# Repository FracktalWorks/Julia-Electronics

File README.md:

# Julia-Electronics
Boards and other electronics for Julia 2018 Series of 3D Printers( Extended, Advanced, Intermediate, Classic)

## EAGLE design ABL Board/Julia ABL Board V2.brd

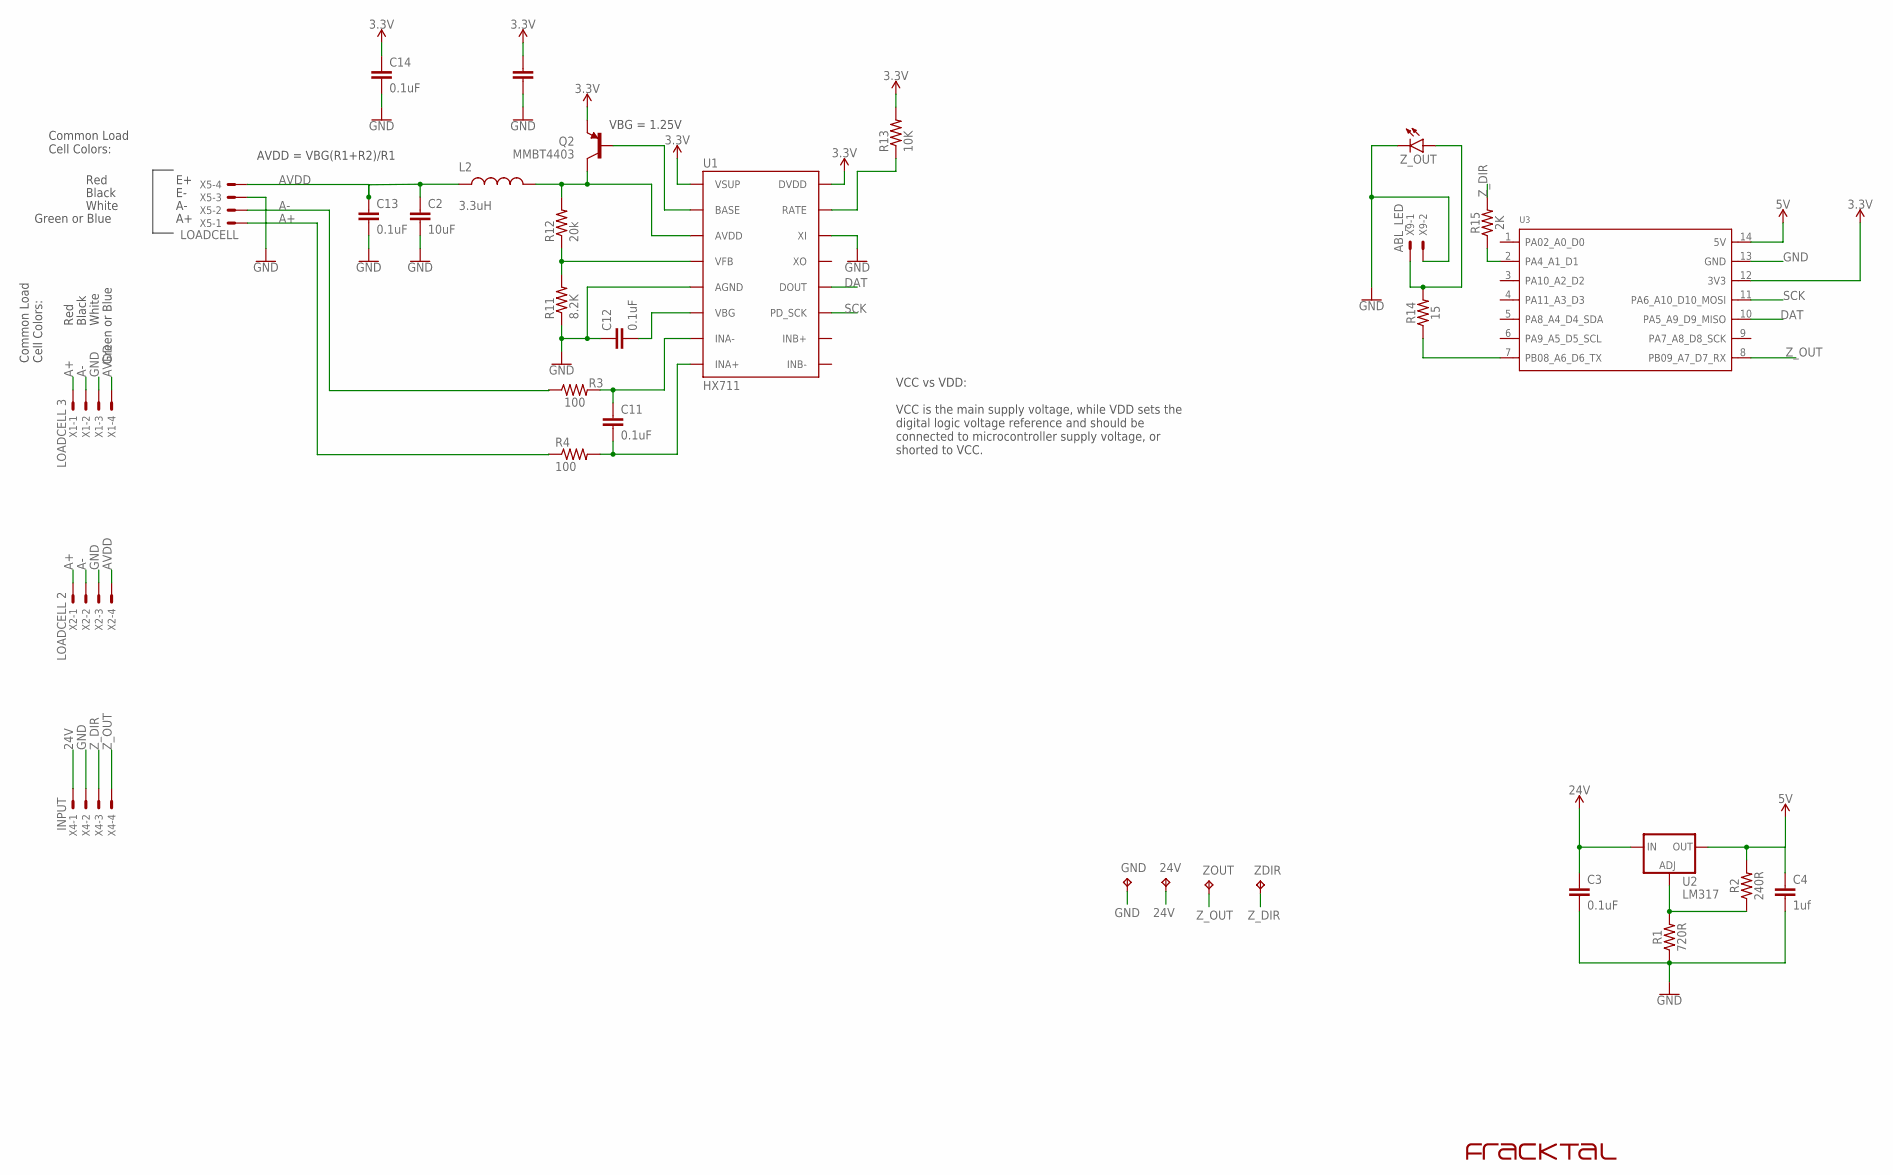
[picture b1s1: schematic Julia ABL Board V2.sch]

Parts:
24V: TPB2,54; B2,54
C1, C2: 10uF; 1210
C3: 0.1uF; 0603
C4: 1uf; 0603
C11, C12, C13, C14: 0.1uF; 0603-CAP
GND: TPB2,54; B2,54
L2: 3.3uH; 0805
Q2: MMBT4403; SOT23-3
R1: 720R; 0603
R2: 240R; 0603
R3, R4: 100; 0603-RES
R11: 8.2K; 0603-RES
R12: 20k; 0603-RES
R13: 10K; 0603-RES
R14: 15; 0603
R15: 2K; 0603
U1: HX711; SO16
U2: LM317; SOT223
U3: MOUDLE-SEEEDUINO-XIAO; MOUDLE14P-2.54-21X17.8MM
U$2: FRACKTALLOGO
X1: LOADCELL 3; JST-XH-04-PACKAGE-LONG-PAD
X2: LOADCELL 2; JST-XH-04-PACKAGE-LONG-PAD
X4: INPUT; JST-XH-04-PACKAGE-LONG-PAD
X5: LOADCELL; JST-XH-04-PACKAGE-LONG-PAD
X9: ABL_LED; JST-XH-02-PACKAGE-LONG-PAD
ZDIR: TPB2,54; B2,54
ZOUT: TPB2,54; B2,54
Z_OUT: LEDSML0603; SML0603

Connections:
3.3V: C1.1, C14.1, Q2.2 (E), R13.2, U1.1 (VSUP), U1.16 (DVDD), U3.12 (3V3)
5V: C4.1, R2.2, U2.2 (OUT), U3.14 (5V)
24V: 24V.TP, C3.1, U2.3 (IN), X4.1
A+: R4.1, X1.1, X2.1, X5.1
A-: R3.1, X1.2, X2.2, X5.2
ADJ: R1.2, R2.1, U2.1 (ADJ)
AVDD: C2.1, C13.1, L2.1, X1.4, X2.4, X5.4
DAT: U1.12 (DOUT), U3.10 (PA5_A9_D9_MISO)
GND: C1.2, C2.2, C3.2, C4.2, C12.1, C13.2, C14.2, GND.TP, R1.1, R11.1, U1.5 (AGND), U1.14 (XI), U3.13 (GND), X1.3, X2.3, X4.2, X5.3, X9.2, Z_OUT.C
unnamed: Q2.1 (B), U1.2 (BASE)
unnamed: R11.2, R12.1, U1.4 (VFB)
unnamed: C12.2, U1.6 (VBG)
unnamed: L2.2, Q2.3 (C), R12.2, U1.3 (AVDD)
unnamed: R13.1, U1.15 (RATE)
unnamed: C11.1, R3.2, U1.7 (INA-)
unnamed: C11.2, R4.2, U1.8 (INA+)
unnamed: R14.2, X9.1, Z_OUT.A
unnamed: R14.1, U3.7 (PB08_A6_D6_TX)
unnamed: R15.1, U3.2 (PA4_A1_D1)
SCK: U1.11 (PD_SCK), U3.11 (PA6_A10_D10_MOSI)
Z_DIR: R15.2, X4.3, ZDIR.TP
Z_OUT: U3.8 (PB09_A7_D7_RX), X4.4, ZOUT.TP

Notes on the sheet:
Red
Black
White
Green or Blue
Common Load Cell Colors:
VBG = 1.25V
AVDD = VBG(R1+R2)/R1
VCC vs VDD: VCC is the main supply voltage, while VDD sets the digital logic voltage reference and should be connected to microcontroller supply voltage, or shorted to VCC.

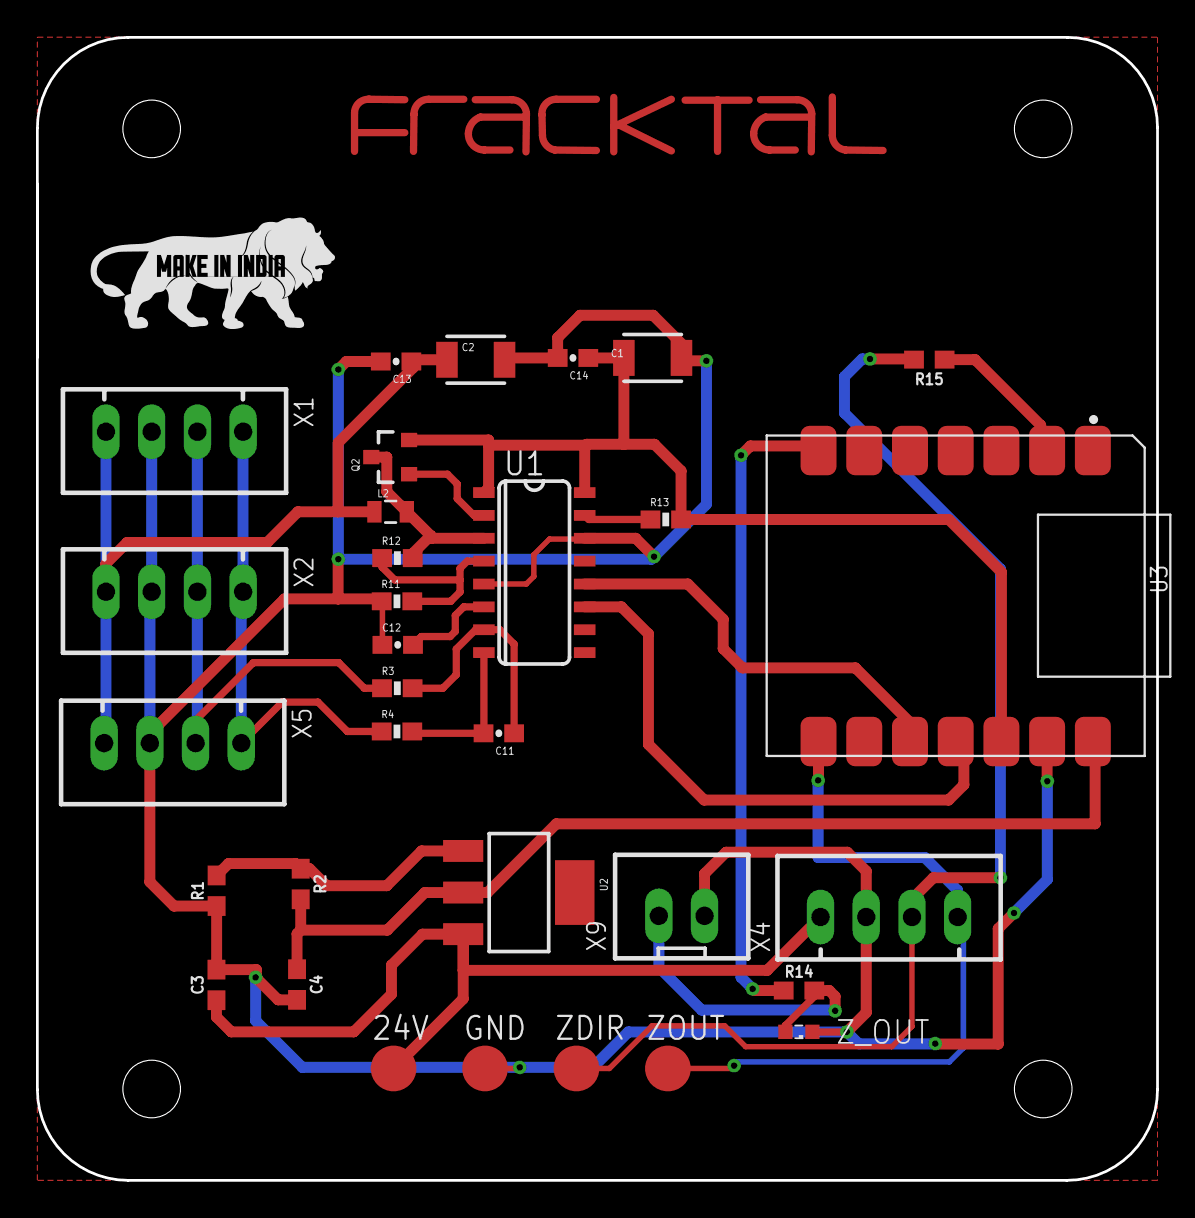
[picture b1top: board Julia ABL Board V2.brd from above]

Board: 2 copper layers, 62.2 x 63.5 mm, 34 parts (0 on the bottom side), 22 nets.

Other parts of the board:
U$1: MAKEININDIA

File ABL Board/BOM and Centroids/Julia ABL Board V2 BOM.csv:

Qty,Designator,Footprint,Comment,LCSC Part #,Description,Value
1,Z_OUT,SML0603,LEDSML0603,,LED,
1,U3,MOUDLE14P-2.54-21X17.8MM,MOUDLE-SEEEDUINO-XIAO,,,
1,R1,603,RESISTOR0603,,Generic Resistor Package, 720R
4,"C11, C12, C13, C14",0603-CAP,0.1UF-25V-5%(0603),,CAP-08604,0.1uF
1,C3,603,9.0PF-0603-50V-10%,,9.0pF ceramic capacitors,0.1uF
2,"R3, R4",0603-RES,100OHM-1/10W-1%(0603),,RES-07863,100
1,R13,0603-RES,10KOHM-1/10W-1%(0603)0603,,RES-00824,10K
2,"C1, C2",1210,10UF50V20%(1210),,CAP-09824,10uF
1,R14,603,RESISTOR0603,,Generic Resistor Package,15
1,C4,603,9.0PF-0603-50V-10%,,9.0pF ceramic capacitors,1uf
1,R12,0603-RES,20KOHM1/10W1%(0603),,RES-09383,20k
1,R2,603,RESISTOR0603,,Generic Resistor Package,240R
1,R15,603,RESISTOR0603,,Generic Resistor Package,2K
1,L2,805,INDUCTOR0805-IND,,Inductors,3.3uH
1,R11,0603-RES,8.2KOHM-1/10W-5%(0603),,RES-10646,8.2K
1,X9,JST-XH-02-PACKAGE-LONG-PAD,JST-XH-02-PIN-LONG-PAD,,JST XH Connector 2 Pin,ABL_LED
1,U$2,FRACKTALLOGO,FRACKTALLOGO,,,FRACKTALLOGO
1,U1,SO16,HX711HX711,,,HX711
1,X4,JST-XH-04-PACKAGE-LONG-PAD,JST-XH-04-PIN-LONG-PAD,,JST XH Connector 2 Pin,INPUT
1,U2,SOT223,V_REG_317SMD,,Voltage Regulator,LM317
1,X5,JST-XH-04-PACKAGE-LONG-PAD,JST-XH-04-PIN-LONG-PAD,,JST XH Connector 2 Pin,LOADCELL
1,X2,JST-XH-04-PACKAGE-LONG-PAD,JST-XH-04-PIN-LONG-PAD,,JST XH Connector 2 Pin,LOADCELL 2
1,X1,JST-XH-04-PACKAGE-LONG-PAD,JST-XH-04-PIN-LONG-PAD,,JST XH Connector 2 Pin,LOADCELL 3
1,Q2,SOT23-3,TRANSISTOR_PNPMMBT4403,,Generic PNP BJT,MMBT4403
4,"24V, GND, ZDIR, ZOUT","B2,54","TPB2,54",,Test pad,"TPB2,54"

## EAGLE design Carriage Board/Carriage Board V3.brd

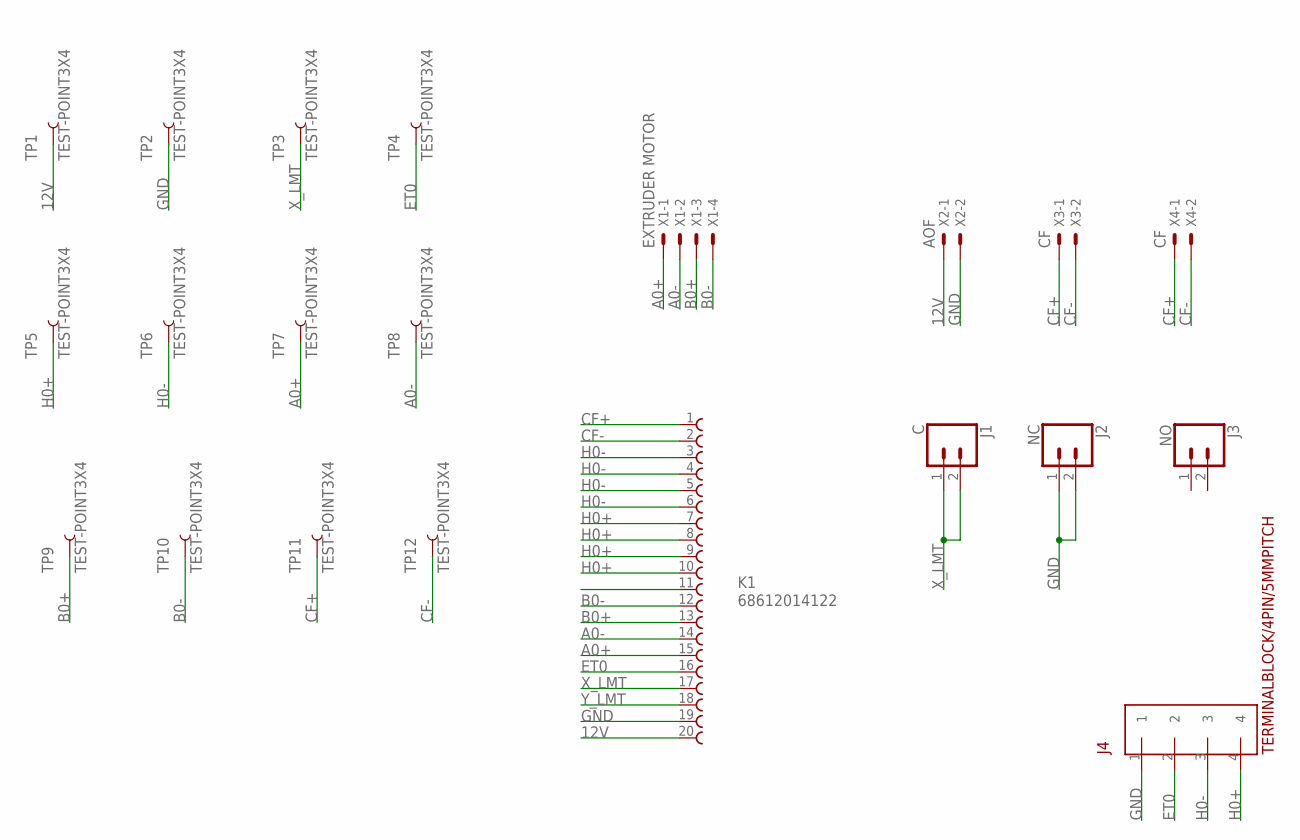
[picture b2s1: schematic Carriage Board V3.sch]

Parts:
J1: C; 1X02
J2: NC; 1X02
J3: NO; 1X02
J4: TERMINALBLOCK/4PIN/5MMPITCH; TERMINALBLOCK/TOYO/4PIN/5MMPITCH
K1: 68612014122
TP1, TP2, TP3, TP4, TP5, TP6, TP7, TP8, TP9, TP10, TP11, TP12: TEST-POINT3X4; PAD.03X.04
X1: EXTRUDER MOTOR; JST-XH-04-PACKAGE-LONG-PAD
X2: AOF; JST-XH-02-PACKAGE-LONG-PAD
X3, X4: CF; JST-XH-02-PACKAGE-LONG-PAD

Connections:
12V: K1.20, TP1.P$1, X2.1
A0+: K1.15, TP7.P$1, X1.1
A0-: K1.14, TP8.P$1, X1.2
B0+: K1.13, TP9.P$1, X1.3
B0-: K1.12, TP10.P$1, X1.4
CF+: K1.1, TP11.P$1, X3.1, X4.1
CF-: K1.2, TP12.P$1, X3.2, X4.2
ET0: J4.2, K1.16, TP4.P$1
GND: J2.1, J2.2, J4.1, K1.19, TP2.P$1, X2.2
H0+: J4.4, K1.7, K1.8, K1.9, K1.10, TP5.P$1
H0-: J4.3, K1.3, K1.4, K1.5, K1.6, TP6.P$1
X_LMT: J1.1, J1.2, K1.17, TP3.P$1
Y_LMT: K1.18

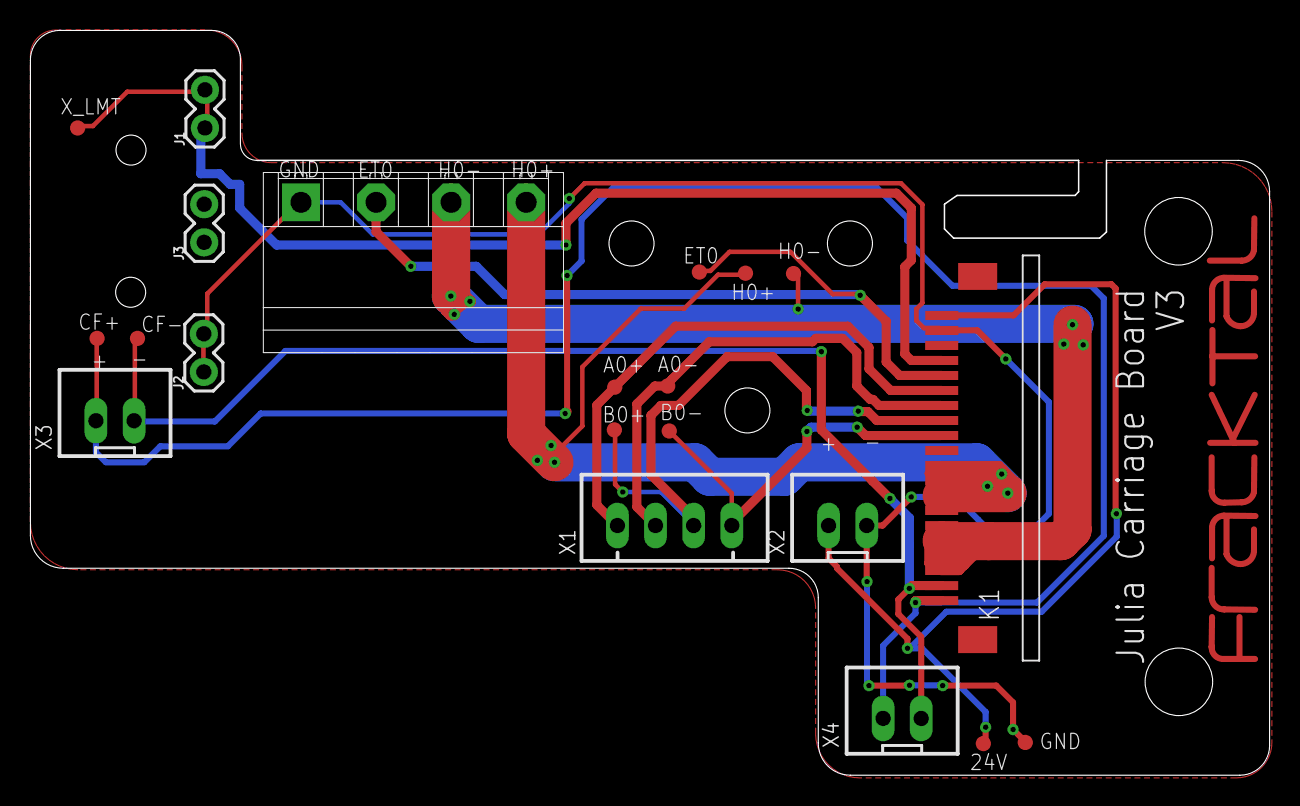
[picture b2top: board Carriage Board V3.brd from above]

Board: 2 copper layers, 82.5 x 49.6 mm, 22 parts (0 on the bottom side), 12 nets.

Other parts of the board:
U$1: FRACKTALLOGO

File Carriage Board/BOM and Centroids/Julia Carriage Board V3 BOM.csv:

Qty,Designator,Footprint,Comment,LCSC Part #,Description,Value
1,K1,68612014122,68612014122,,"WR-FPC 1.00mm SMT ZIF Horizontal Top Contact, 20 Pins=>Code : Con_FPC_ZIF_1.00_68612014122",68612014122
1,X2,JST-XH-02-PACKAGE-LONG-PAD,JST-XH-02-PIN-LONG-PAD,,JST XH Connector 2 Pin,AOF
1,J1,1X02,CONN_02,,Multi connection point. Often used as Generic Header-pin footprint for 0.1 inch spaced/style header connections,C
2,"X3, X4",JST-XH-02-PACKAGE-LONG-PAD,JST-XH-02-PIN-LONG-PAD,,JST XH Connector 2 Pin,CF
1,X1,JST-XH-04-PACKAGE-LONG-PAD,JST-XH-04-PIN-LONG-PAD,,JST XH Connector 2 Pin,EXTRUDER MOTOR
1,J2,1X02,CONN_02,,Multi connection point. Often used as Generic Header-pin footprint for 0.1 inch spaced/style header connections,NC
1,J3,1X02,CONN_02,,Multi connection point. Often used as Generic Header-pin footprint for 0.1 inch spaced/style header connections,NO
1,J4,TERMINALBLOCK/TOYO/4PIN/5MMPITCH,TERMINALBLOCK/4PIN/5MMPITCH,,,TERMINALBLOCK/4PIN/5MMPITCH
12,"TP1, TP2, TP3, TP4, TP5, TP6, TP7, TP8, TP9, TP10, TP11, TP12",PAD.03X.04,TEST-POINT3X4,,SparkFun Test Points,TEST-POINT3X4

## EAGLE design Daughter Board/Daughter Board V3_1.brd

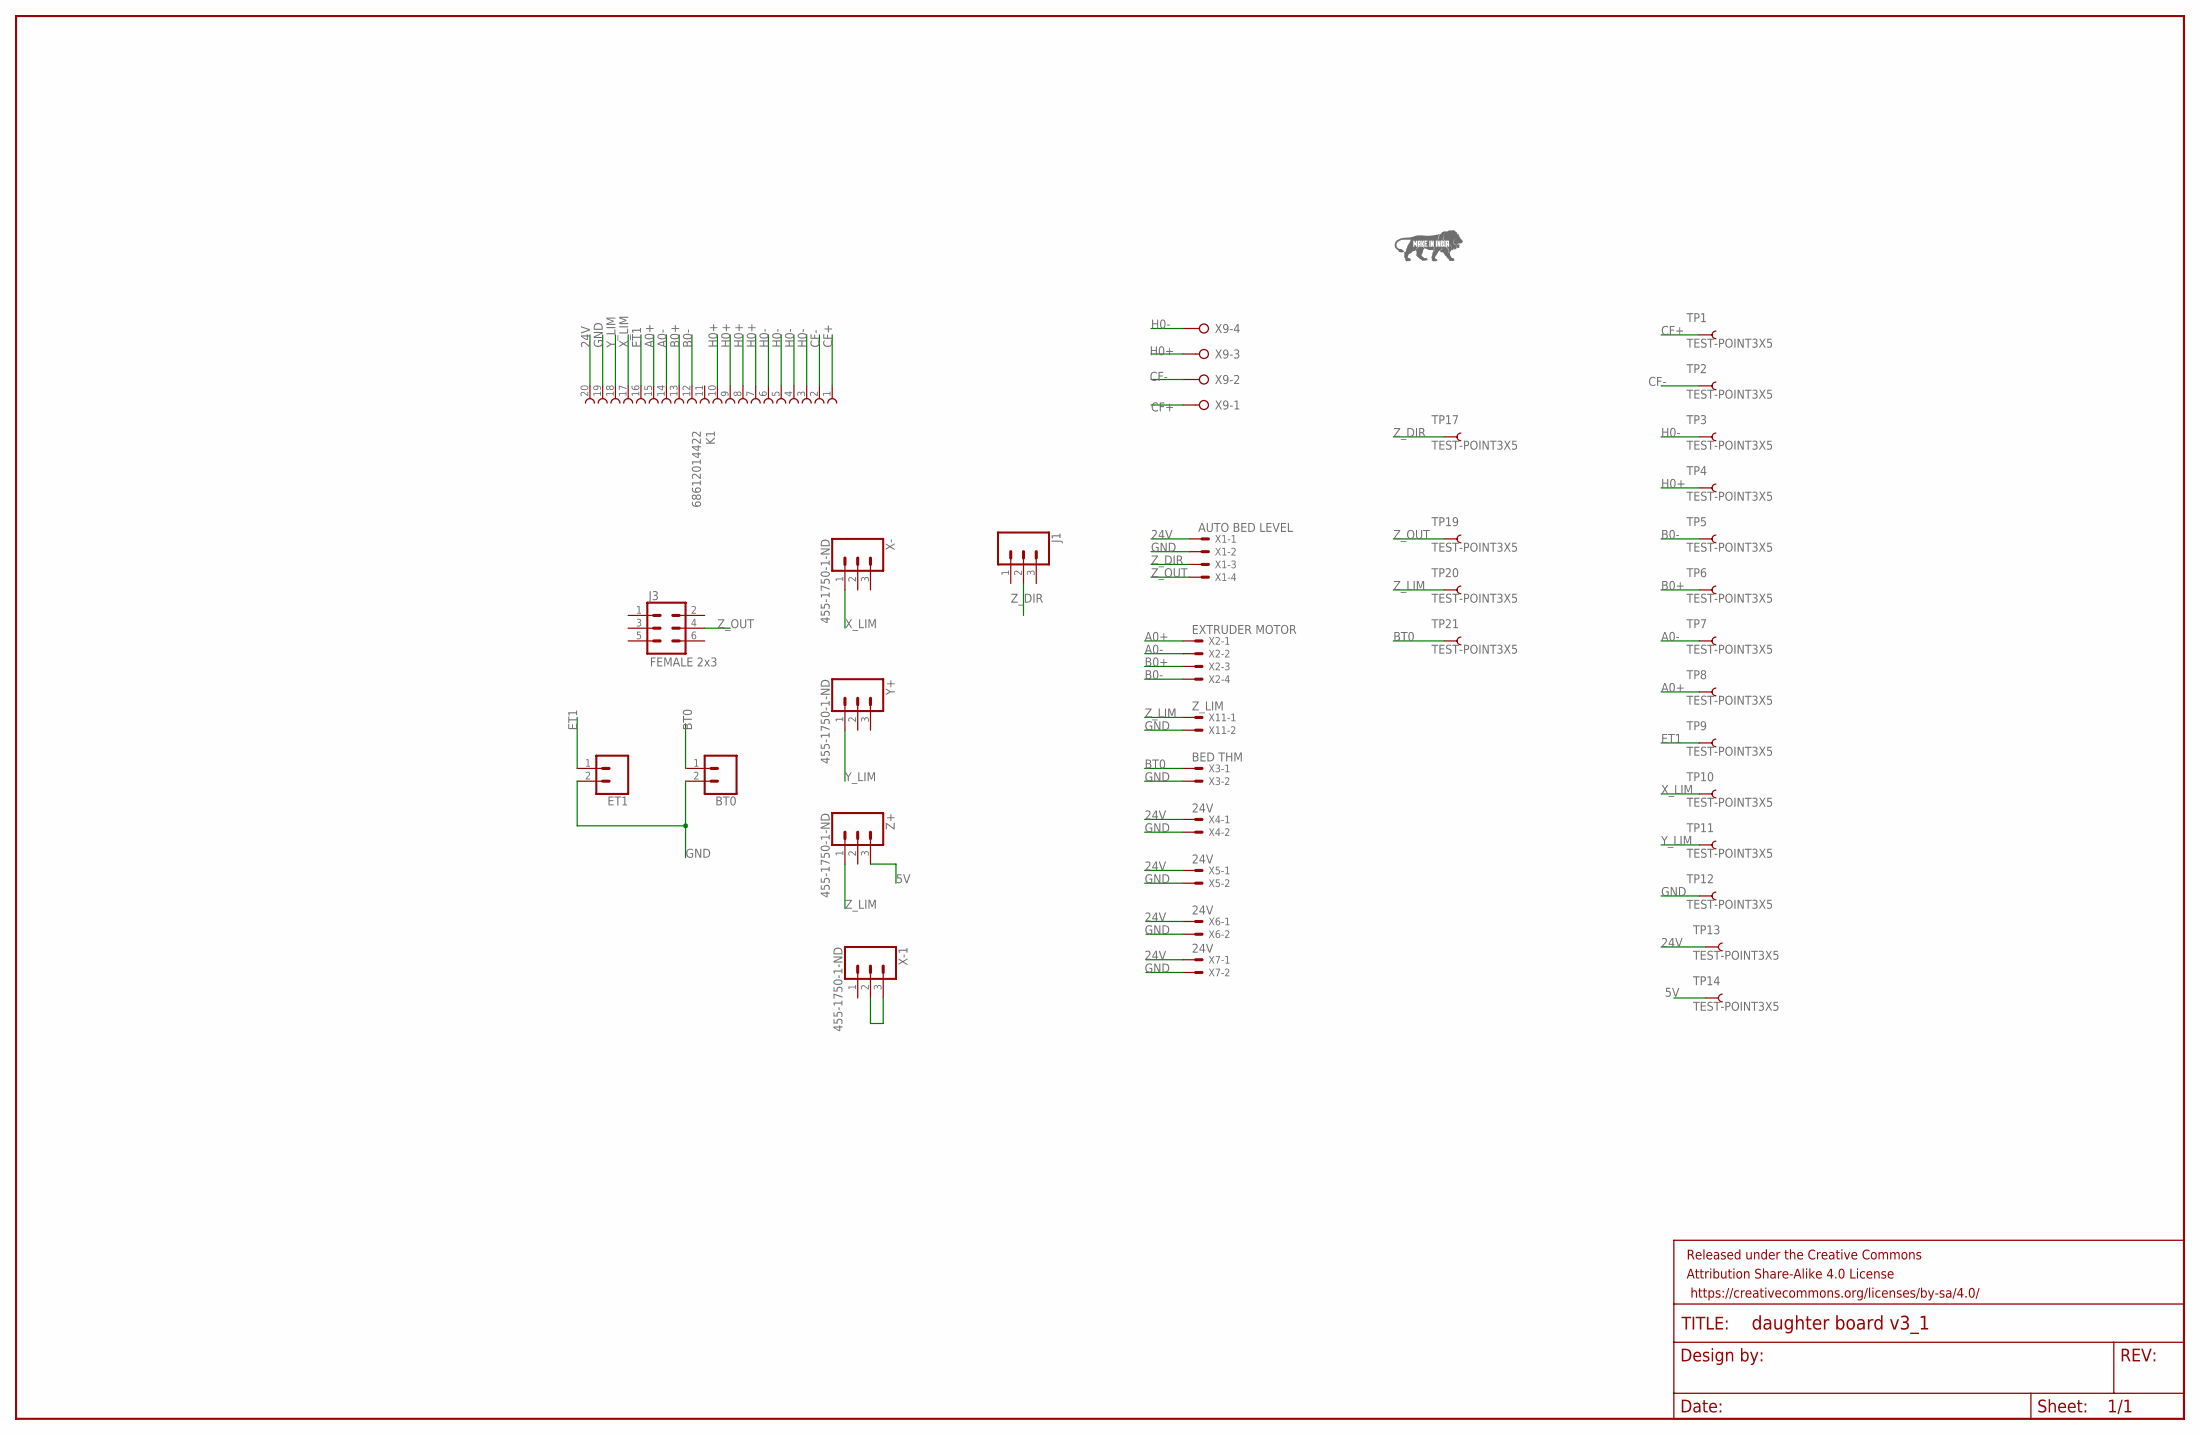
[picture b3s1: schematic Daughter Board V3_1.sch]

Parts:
BT0: CONN_02; 1X02
ET1: CONN_02; 1X02
FRAME1: FRAME-LEDGER; CREATIVE_COMMONS
J1: 455-1750-1-ND; 1X03
J3: FEMALE 2x3; 2X3
K1: 68612014422
TP1, TP2, TP3, TP4, TP5, TP6, TP7, TP8, TP9, TP10, TP11, TP12, TP13, TP14, TP17, TP19, TP20, TP21: TEST-POINT3X5; PAD.03X.05
U$2: MAKEININDIA
X1: AUTO BED LEVEL; JST-XH-04-PACKAGE-LONG-PAD
X2: EXTRUDER MOTOR; JST-XH-04-PACKAGE-LONG-PAD
X3: BED THM; JST-XH-02-PACKAGE-LONG-PAD
X4, X5, X6, X7: 24V; JST-XH-02-PACKAGE-LONG-PAD
X9: W237-04P; W237-4P
X11: Z_LIM; JST-XH-02-PACKAGE-LONG-PAD
X-, X-1: 455-1750-1-ND; 1X03
Y+: 455-1750-1-ND; 1X03
Z+: 455-1750-1-ND; 1X03

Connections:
5V: TP14.P$1, Z+.3
24V: K1.20, TP13.P$1, X1.1, X4.1, X5.1, X6.1, X7.1
A0+: K1.15, TP8.P$1, X2.1
A0-: K1.14, TP7.P$1, X2.2
B0+: K1.13, TP6.P$1, X2.3
B0-: K1.12, TP5.P$1, X2.4
BT0: BT0.1, TP21.P$1, X3.1
CF+: K1.1, TP1.P$1, X9.1
CF-: K1.2, TP2.P$1, X9.2
ET1: ET1.1, K1.16, TP9.P$1
GND: BT0.2, ET1.2, K1.19, TP12.P$1, X1.2, X3.2, X4.2, X5.2, X6.2, X7.2, X11.2
H0+: K1.7, K1.8, K1.9, K1.10, TP4.P$1, X9.3
H0-: K1.3, K1.4, K1.5, K1.6, TP3.P$1, X9.4
unnamed: X-1.2, X-1.3
X_LIM: K1.17, TP10.P$1, X-.1
Y_LIM: K1.18, TP11.P$1, Y+.1
Z_DIR: J1.2, TP17.P$1, X1.3
Z_LIM: TP20.P$1, X11.1, Z+.1
Z_OUT: J3.4, TP19.P$1, X1.4

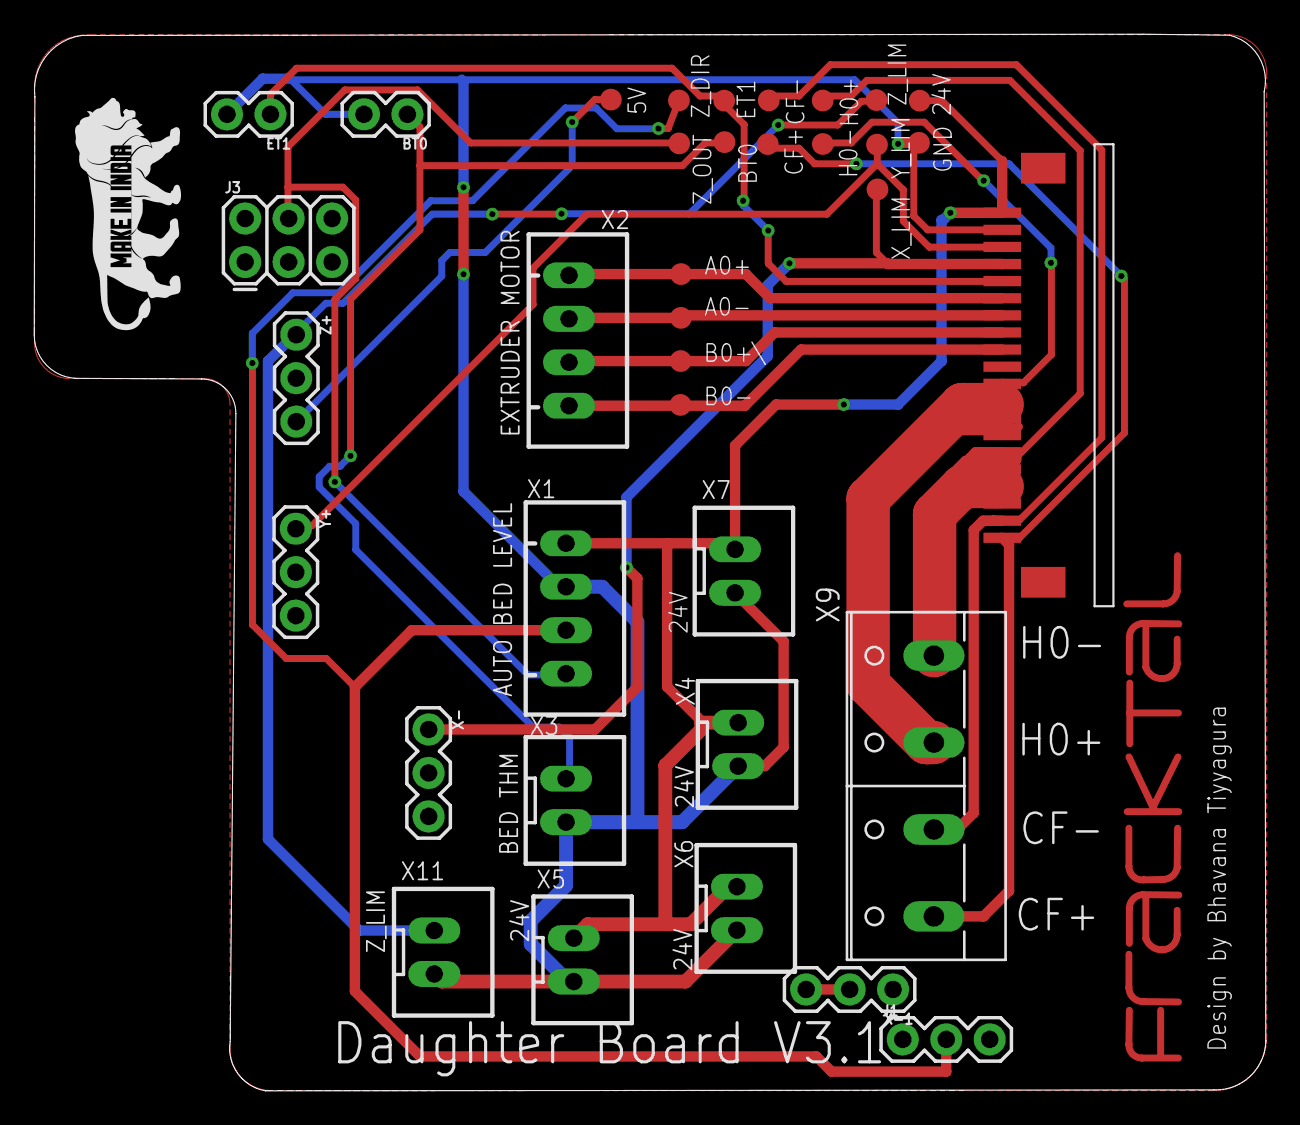
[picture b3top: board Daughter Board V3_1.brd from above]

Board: 2 copper layers, 72.0 x 61.8 mm, 39 parts (0 on the bottom side), 19 nets.

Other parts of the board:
U$1: FRACKTALLOGO

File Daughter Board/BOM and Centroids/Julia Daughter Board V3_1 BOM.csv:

Qty,Designator,Footprint,Comment,LCSC Part #,Description,Value
2,"BT0, ET1",1X02,CONN_02,,Multi connection point. Often used as Generic Header-pin footprint for 0.1 inch spaced/style header connections,
1,X9,W237-4P,W237-04P,,WAGO SREW CLAMP,
4,"X4, X5, X6, X7",JST-XH-02-PACKAGE-LONG-PAD,JST-XH-02-PIN-LONG-PAD,,JST XH Connector 2 Pin,24V
5,"J1, X-, X-1, Y+, Z+",1X03,CONN_03,,Multi connection point. Often used as Generic Header-pin footprint for 0.1 inch spaced/style header connections,455-1750-1-ND
1,K1,68612014422,68612014422,,"WR-FPC 1.00mm SMT ZIF Horizontal Bottom Contact, 20 Pins=>Code : Con_FPC_ZIF_1.00_68612014422",68612014422
1,X1,JST-XH-04-PACKAGE-LONG-PAD,JST-XH-04-PIN-LONG-PAD,,JST XH Connector 2 Pin,AUTO BED LEVEL
1,X3,JST-XH-02-PACKAGE-LONG-PAD,JST-XH-02-PIN-LONG-PAD,,JST XH Connector 2 Pin,BED THM
1,X2,JST-XH-04-PACKAGE-LONG-PAD,JST-XH-04-PIN-LONG-PAD,,JST XH Connector 2 Pin,EXTRUDER MOTOR
1,J3,2X3,CONN_03X2FEMALE,,Multi connection point. Often used as Generic Header-pin footprint for 0.1 inch spaced/style header connections,FEMALE 2x3
1,FRAME1,CREATIVE_COMMONS,FRAME-LEDGER,,Schematic Frame - Ledger,FRAME-LEDGER
1,U$2,MAKEININDIA,MAKEININDIA,,,MAKEININDIA
18,"TP1, TP2, TP3, TP4, TP5, TP6, TP7, TP8, TP9, TP10, TP11, TP12, TP13, TP14, TP17, TP19, TP20, TP21",PAD.03X.05,TEST-POINT3X5,,SparkFun Test Points,TEST-POINT3X5
1,X11,JST-XH-02-PACKAGE-LONG-PAD,JST-XH-02-PIN-LONG-PAD,,JST XH Connector 2 Pin,Z_LIM

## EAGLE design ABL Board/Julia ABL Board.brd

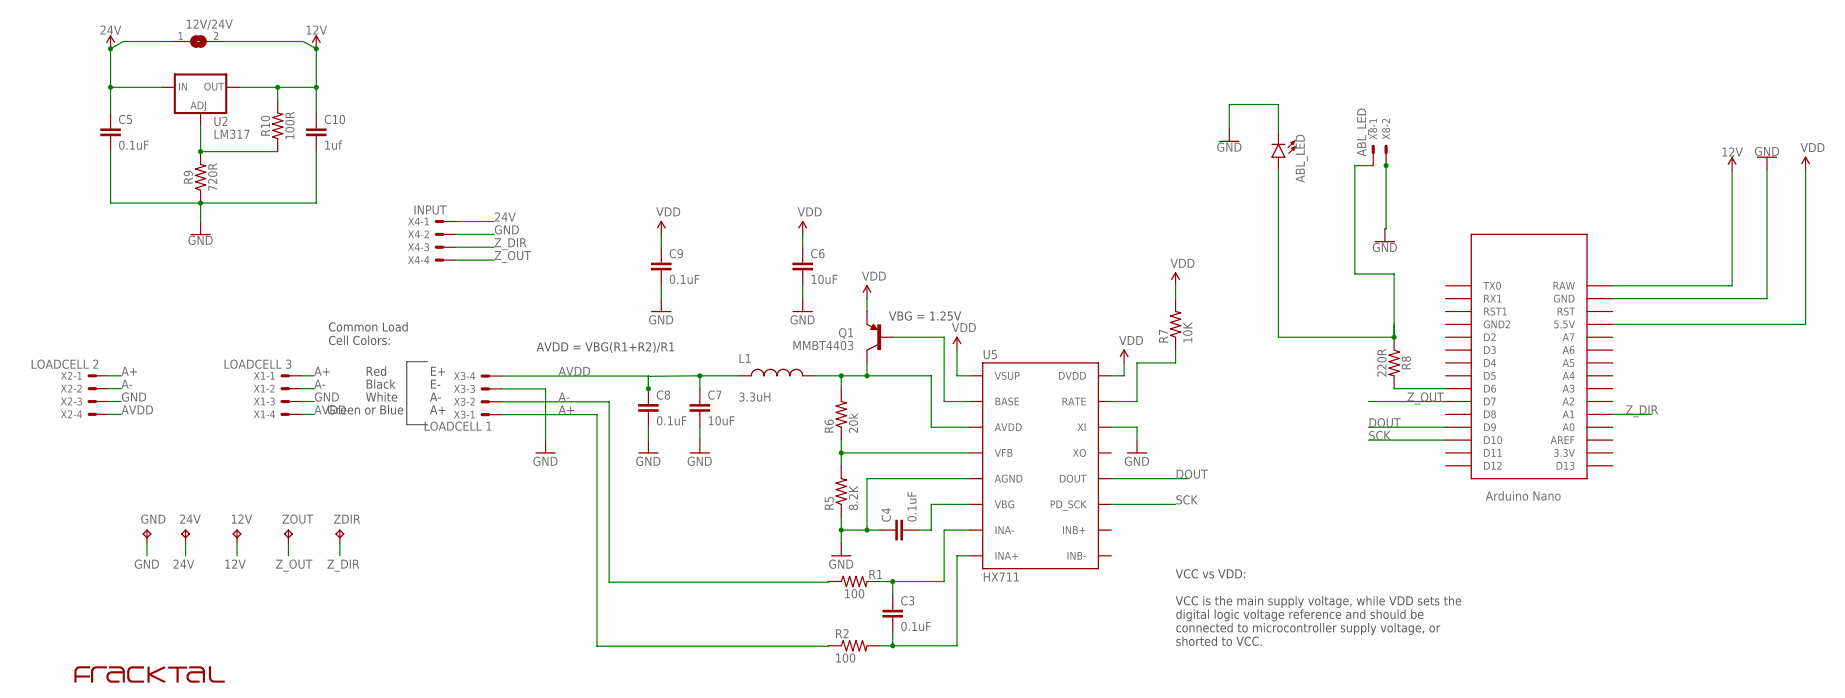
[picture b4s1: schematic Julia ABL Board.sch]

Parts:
12V, 24V: TPB2,54; B2,54
12V/24V: SJ
ABL_LED: LED-3MM-NO_SILK; LED_3MM-NS
C3, C4, C8, C9: 0.1uF; 0603-CAP
C5: 0.1uF; 0603
C6, C7: 10uF; 1210
C10: 1uf; 0603
GND: TPB2,54; B2,54
L1: 3.3uH; 0805
Q1: MMBT4403; SOT23-3
R1, R2: 100; 0603-RES
R5: 8.2K; 0603-RES
R6: 20k; 0603-RES
R7: 10K; 0603-RES
R8: 220R; 0603
R9: 720R; 0603
R10: 100R; 0603
U2: LM317; SOT223
U5: HX711; SO16
U$1: NANO
U$2: FRACKTALLOGO
X1: LOADCELL 3; JST-XH-04-PACKAGE-LONG-PAD
X2: LOADCELL 2; JST-XH-04-PACKAGE-LONG-PAD
X3: LOADCELL 1; JST-XH-04-PACKAGE-LONG-PAD
X4: INPUT; JST-XH-04-PACKAGE-LONG-PAD
X8: ABL_LED; JST-XH-02-PACKAGE-LONG-PAD
ZDIR: TPB2,54; B2,54
ZOUT: TPB2,54; B2,54

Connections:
12V: 12V.TP, 12V/24V.2, C10.1, R10.2, U2.2 (OUT), U$1.RAW
24V: 12V/24V.1, 24V.TP, C5.1, U2.3 (IN), X4.1
A+: R2.1, X1.1, X2.1, X3.1
A-: R1.1, X1.2, X2.2, X3.2
ADJ1: R9.2, R10.1, U2.1 (ADJ)
AVDD: C7.1, C8.1, L1.1, X1.4, X2.4, X3.4
DOUT: U5.12 (DOUT), U$1.D9
GND: ABL_LED.K (C), C4.1, C5.2, C6.2, C7.2, C8.2, C9.2, C10.2, GND.TP, R5.1, R9.1, U5.5 (AGND), U5.14 (XI), U$1.GND, X1.3, X2.3, X3.3, X4.2, X8.2
unnamed: R8.2, U$1.D6
unnamed: R7.1, U5.15 (RATE)
unnamed: C3.1, R1.2, U5.7 (INA-)
unnamed: Q1.1 (B), U5.2 (BASE)
unnamed: L1.2, Q1.3 (C), R6.2, U5.3 (AVDD)
unnamed: R5.2, R6.1, U5.4 (VFB)
unnamed: C4.2, U5.6 (VBG)
unnamed: C3.2, R2.2, U5.8 (INA+)
unnamed: ABL_LED.A, R8.1, X8.1
SCK: U5.11 (PD_SCK), U$1.D10
VDD: C6.1, C9.1, Q1.2 (E), R7.2, U5.1 (VSUP), U5.16 (DVDD), U$1.5V (5.5V)
Z_DIR: U$1.A1, X4.3, ZDIR.TP
Z_OUT: U$1.D7, X4.4, ZOUT.TP

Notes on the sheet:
VBG = 1.25V
AVDD = VBG(R1+R2)/R1
Red
Black
White
Green or Blue
Common Load Cell Colors:
VCC vs VDD: VCC is the main supply voltage, while VDD sets the digital logic voltage reference and should be connected to microcontroller supply voltage, or shorted to VCC.

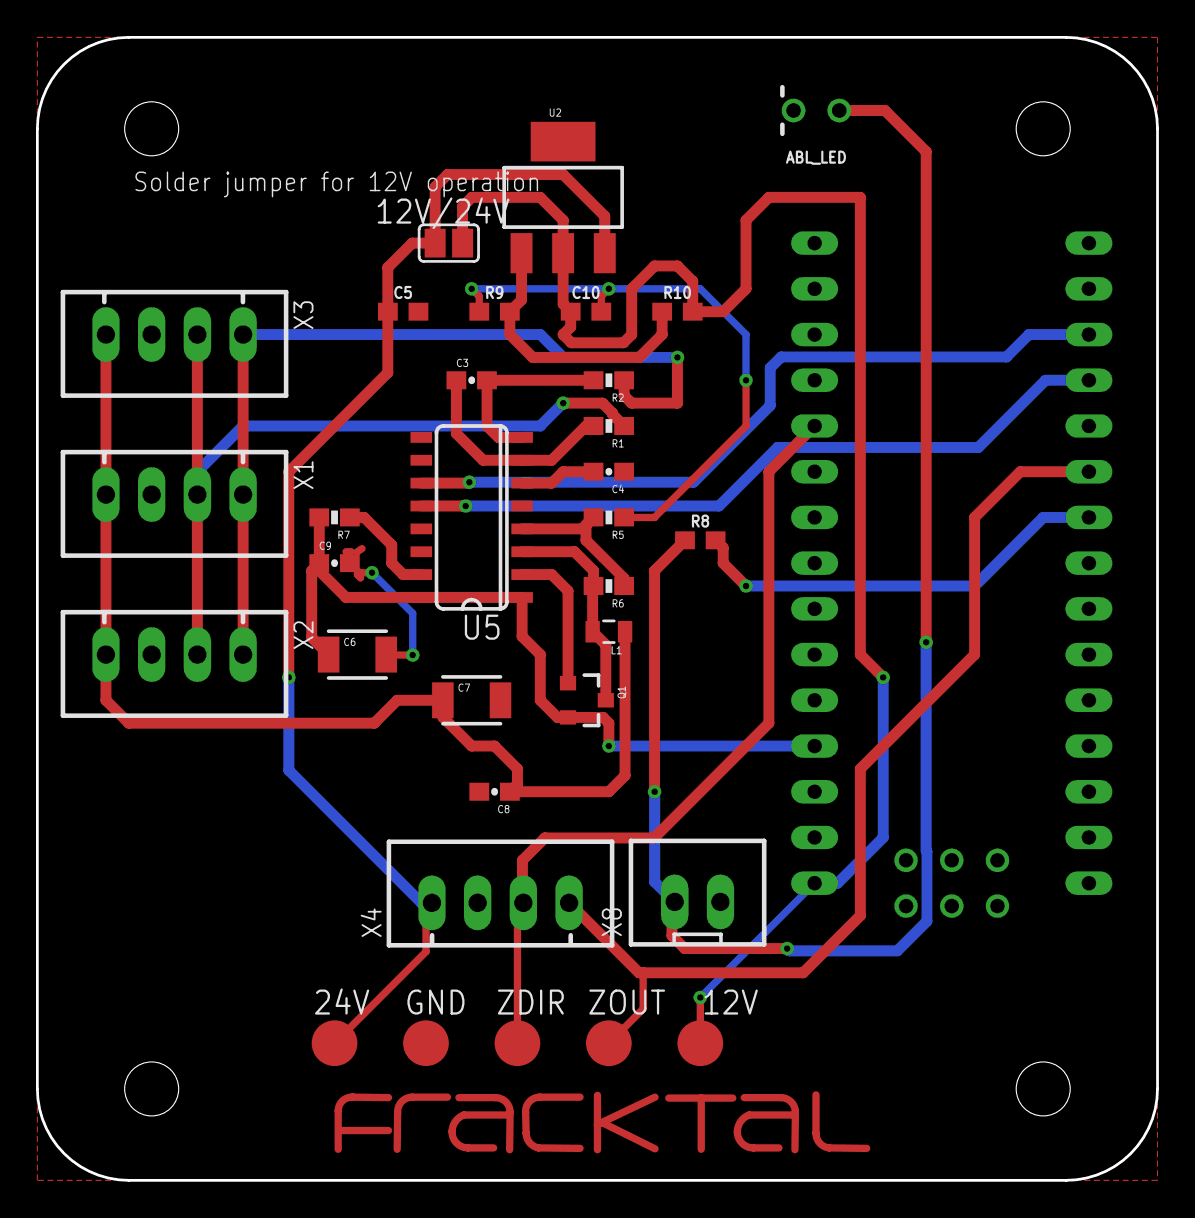
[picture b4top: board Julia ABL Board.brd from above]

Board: 2 copper layers, 62.2 x 63.5 mm, 34 parts (0 on the bottom side), 21 nets.

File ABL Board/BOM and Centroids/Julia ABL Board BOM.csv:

Qty,Designator,Footprint,Comment,LCSC Part #,Description,Value
1,ABL_LED,LED_3MM-NS,LED-3MM-NO_SILK,,LED (Generic),
1,12V/24V,SJ,SJ,,SMD solder JUMPER,
1,R9,603,RESISTOR0603,,Generic Resistor Package, 720R
4,"C3, C4, C8, C9",0603-CAP,0.1UF-25V-5%(0603),,CAP-08604,0.1uF
1,C5,603,9.0PF-0603-50V-10%,,9.0pF ceramic capacitors,0.1uF
2,"R1, R2",0603-RES,100OHM-1/10W-1%(0603),,RES-07863,100
1,R10,603,RESISTOR0603,,Generic Resistor Package,100R
1,R7,0603-RES,10KOHM-1/10W-1%(0603)0603,,RES-00824,10K
2,"C6, C7",1210,10UF50V20%(1210),,CAP-09824,10uF
1,C10,603,9.0PF-0603-50V-10%,,9.0pF ceramic capacitors,1uf
1,R6,0603-RES,20KOHM1/10W1%(0603),,RES-09383,20k
1,R8,603,RESISTOR0603,,Generic Resistor Package,220R
1,L1,805,INDUCTOR0805-IND,,Inductors,3.3uH
1,R5,0603-RES,8.2KOHM-1/10W-5%(0603),,RES-10646,8.2K
1,X8,JST-XH-02-PACKAGE-LONG-PAD,JST-XH-02-PIN-LONG-PAD,,JST XH Connector 2 Pin,ABL_LED
1,U$2,FRACKTALLOGO,FRACKTALLOGO,,,FRACKTALLOGO
1,U5,SO16,HX711HX711,,,HX711
1,X4,JST-XH-04-PACKAGE-LONG-PAD,JST-XH-04-PIN-LONG-PAD,,JST XH Connector 2 Pin,INPUT
1,U2,SOT223,V_REG_317SMD,,Voltage Regulator,LM317
1,X3,JST-XH-04-PACKAGE-LONG-PAD,JST-XH-04-PIN-LONG-PAD,,JST XH Connector 2 Pin,LOADCELL 1
1,X2,JST-XH-04-PACKAGE-LONG-PAD,JST-XH-04-PIN-LONG-PAD,,JST XH Connector 2 Pin,LOADCELL 2
1,X1,JST-XH-04-PACKAGE-LONG-PAD,JST-XH-04-PIN-LONG-PAD,,JST XH Connector 2 Pin,LOADCELL 3
1,Q1,SOT23-3,TRANSISTOR_PNPMMBT4403,,Generic PNP BJT,MMBT4403
1,U$1,NANO,NANO,,Arduino Nano,NANO
5,"12V, 24V, GND, ZDIR, ZOUT","B2,54","TPB2,54",,Test pad,"TPB2,54"

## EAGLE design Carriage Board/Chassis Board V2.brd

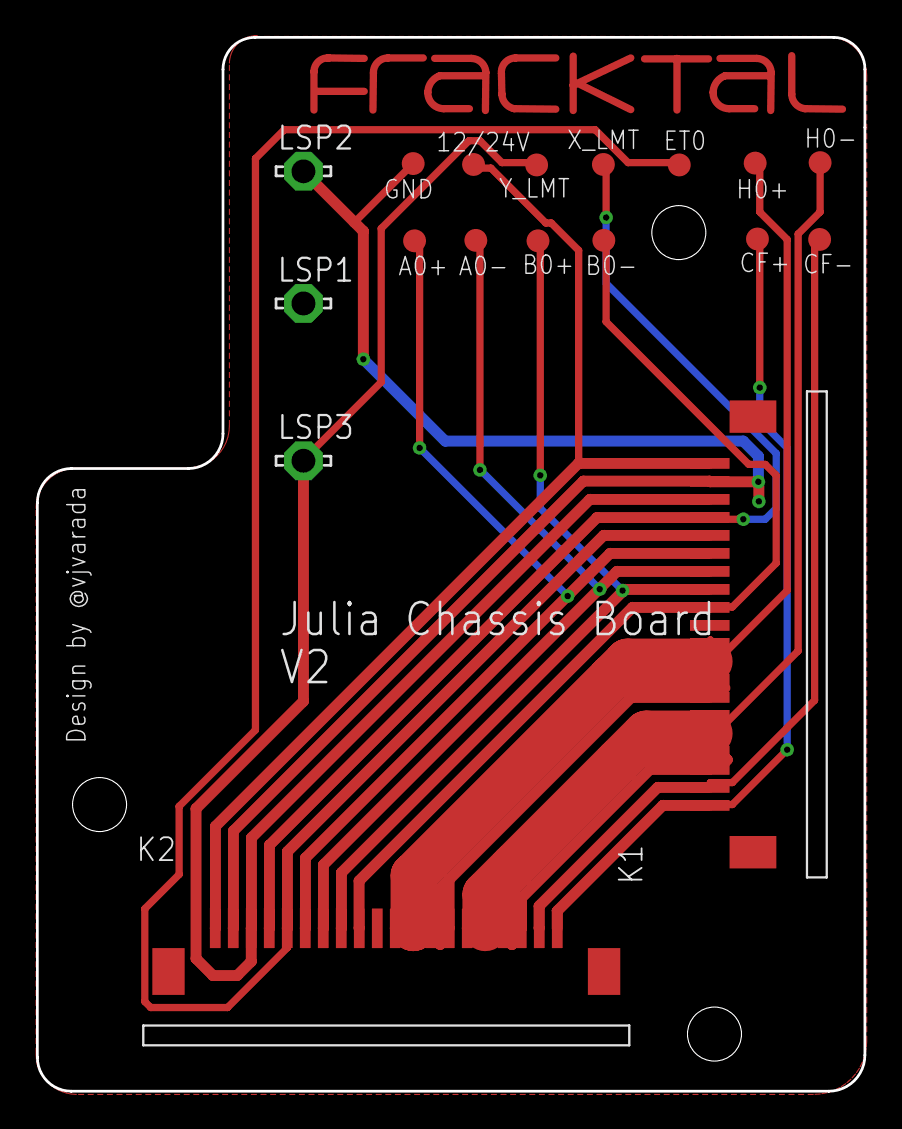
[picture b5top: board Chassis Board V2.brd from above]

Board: 2 copper layers, 46.0 x 58.5 mm, 20 parts (0 on the bottom side), 13 nets.

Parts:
FRAME1: FRAME-LETTER; CREATIVE_COMMONS
K1, K2: 68612014122
LSP1: NO; LSP13
LSP2: NC; LSP13
LSP3: C; LSP13
TP1, TP2, TP3, TP4, TP5, TP6, TP7, TP8, TP9, TP10, TP11, TP12, TP13: TEST-POINT3X5; PAD.03X.05
U$1: FRACKTALLOGO

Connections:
12V: K1.20, K2.1, TP2.P$1
A0+: K1.15, K2.6, TP6.P$1
A0-: K1.14, K2.7, TP7.P$1
B0+: K1.13, K2.8, TP8.P$1
B0-: K1.12, K2.9, TP9.P$1
CF+: K1.1, K2.20, TP13.P$1
CF-: K1.2, K2.19, TP12.P$1
ET0: K1.16, K2.5, TP5.P$1
GND: K1.19, K2.2, LSP2.MP, TP1.P$1
H0+: K1.7, K1.8, K1.9, K1.10, K2.11, K2.12, K2.13, K2.14, TP10.P$1
H0-: K1.3, K1.4, K1.5, K1.6, K2.15, K2.16, K2.17, K2.18, TP11.P$1
X_LMT: K1.17, K2.4, TP4.P$1
Y_LMT: K1.18, K2.3, LSP3.MP, TP3.P$1

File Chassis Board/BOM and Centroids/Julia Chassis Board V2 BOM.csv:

Qty,Designator,Footprint,Comment,LCSC Part #,Description,Value
2,"K1, K2",68612014122,68612014122,,"WR-FPC 1.00mm SMT ZIF Horizontal Top Contact, 20 Pins=>Code : Con_FPC_ZIF_1.00_68612014122",68612014122
1,LSP3,LSP13,LSP13,,"SOLDER PAD drill 1.3 mm, distributor Buerklin, 12H562",C
1,FRAME1,CREATIVE_COMMONS,FRAME-LETTER,,Schematic Frame - Letter,FRAME-LETTER
1,LSP2,LSP13,LSP13,,"SOLDER PAD drill 1.3 mm, distributor Buerklin, 12H562",NC
1,LSP1,LSP13,LSP13,,"SOLDER PAD drill 1.3 mm, distributor Buerklin, 12H562",NO
13,"TP1, TP2, TP3, TP4, TP5, TP6, TP7, TP8, TP9, TP10, TP11, TP12, TP13",PAD.03X.05,TEST-POINT3X5,,SparkFun Test Points,TEST-POINT3X5

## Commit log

2020-01-10 fixed ABL board
2020-01-16 generated ABL board gerbers
2020-01-16 rearraged files
2020-01-16 removed old gerbers
2020-02-29 Added LED to ABL board
2022-01-25 boards for GEN L 2.1
2022-09-25 Added V3
    Changes:
    Position of Control Fan
    Slot for Wire Management
2022-09-25 V3.1 updated
    Added 24V connector, 5V selector connencted
2022-09-27 Updated Boards
2022-11-15 Missing link in the GND wire routing rectified
    The missing link in the GND wire has been rectified and routed consecutively in the Carriage board V3 of the Julia electronics file
2023-02-02 Updated BOM and Centroid files
2023-07-11 Added Julia ABL Board V2 BOM and centroids
2023-07-11 Correction of Julia ABL Board V2 BOM and Centroid files
2023-08-23 Updated ABL V2 design, added Gerber, BOM and Centroids of V2

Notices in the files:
parts and their libraries:
SparkFun-Capacitors: Licensing: Creative Commons ShareAlike 4.0 International - https://creativecommons.org/licenses/by-sa/4.0
Wurth_Elektronik_Electromechanic_FPC_Con: Copyright: Würth Elektronik
SparkFun-Aesthetics: Released under the Creative Commons Attribution Share-Alike 4.0 License
